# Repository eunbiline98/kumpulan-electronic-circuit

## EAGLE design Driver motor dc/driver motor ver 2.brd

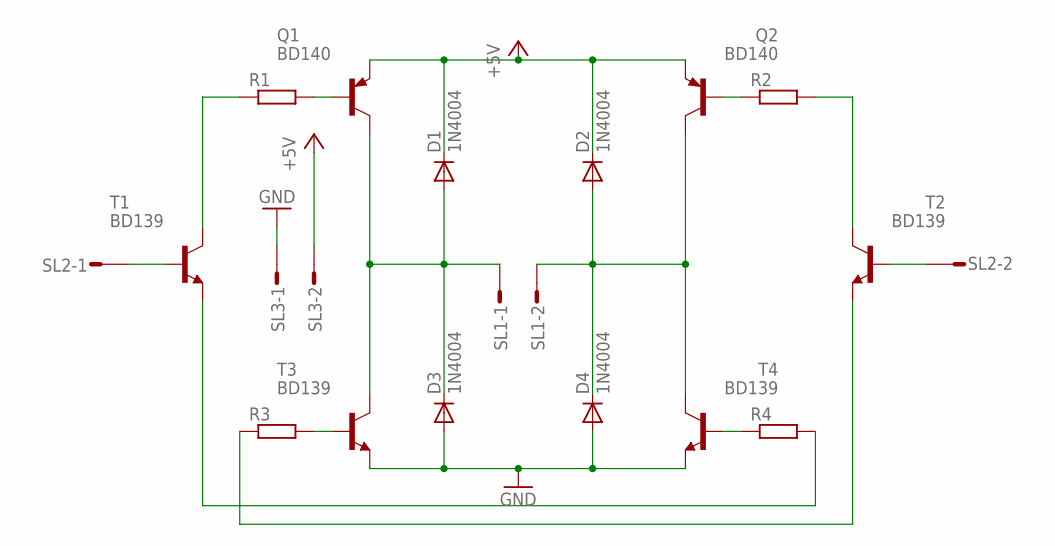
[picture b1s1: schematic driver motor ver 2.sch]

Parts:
D1, D2, D3, D4: 1N4004; DO41-10
Q1, Q2: BD140; TO126
R1, R2, R3, R4: R-EU_0204/5; 0204/5
SL1, SL2, SL3: M02S; 02P
T1, T2, T3, T4: BD139; TO126

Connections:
+5V: D1.C, D2.C, Q1.1 (E), Q2.1 (E), SL3.2
GND: D3.A, D4.A, SL3.1, T3.1 (E), T4.1 (E)
unnamed: Q1.3 (B), R1.2
unnamed: Q2.3 (B), R2.1
unnamed: R3.2, T3.3 (B)
unnamed: SL2.1, T1.3 (B)
unnamed: SL2.2, T2.3 (B)
unnamed: R1.1, T1.2 (C)
unnamed: D1.A, D3.C, Q1.2 (C), SL1.1, T3.2 (C)
unnamed: D2.A, D4.C, Q2.2 (C), SL1.2, T4.2 (C)
unnamed: R4.2, T1.1 (E)
unnamed: R4.1, T4.3 (B)
unnamed: R3.1, T2.1 (E)
unnamed: R2.2, T2.2 (C)

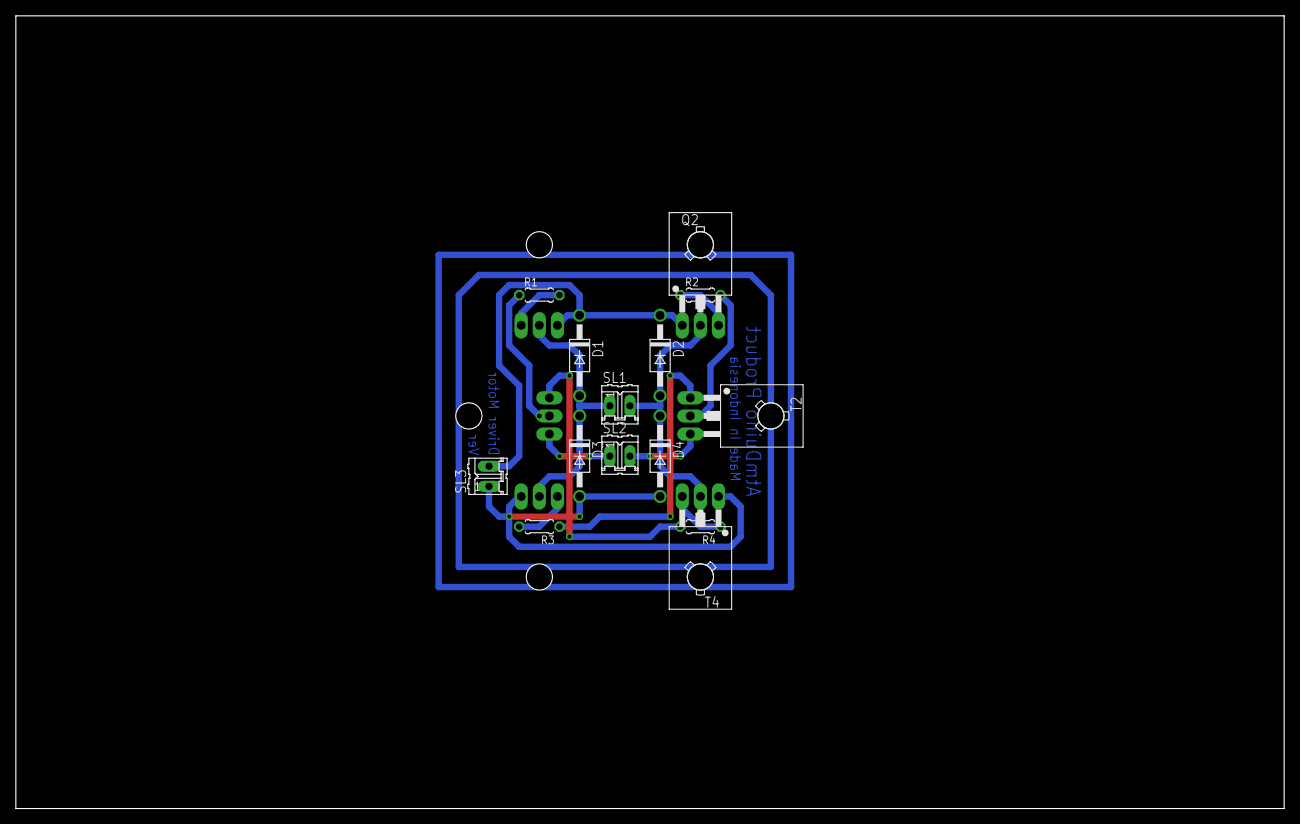
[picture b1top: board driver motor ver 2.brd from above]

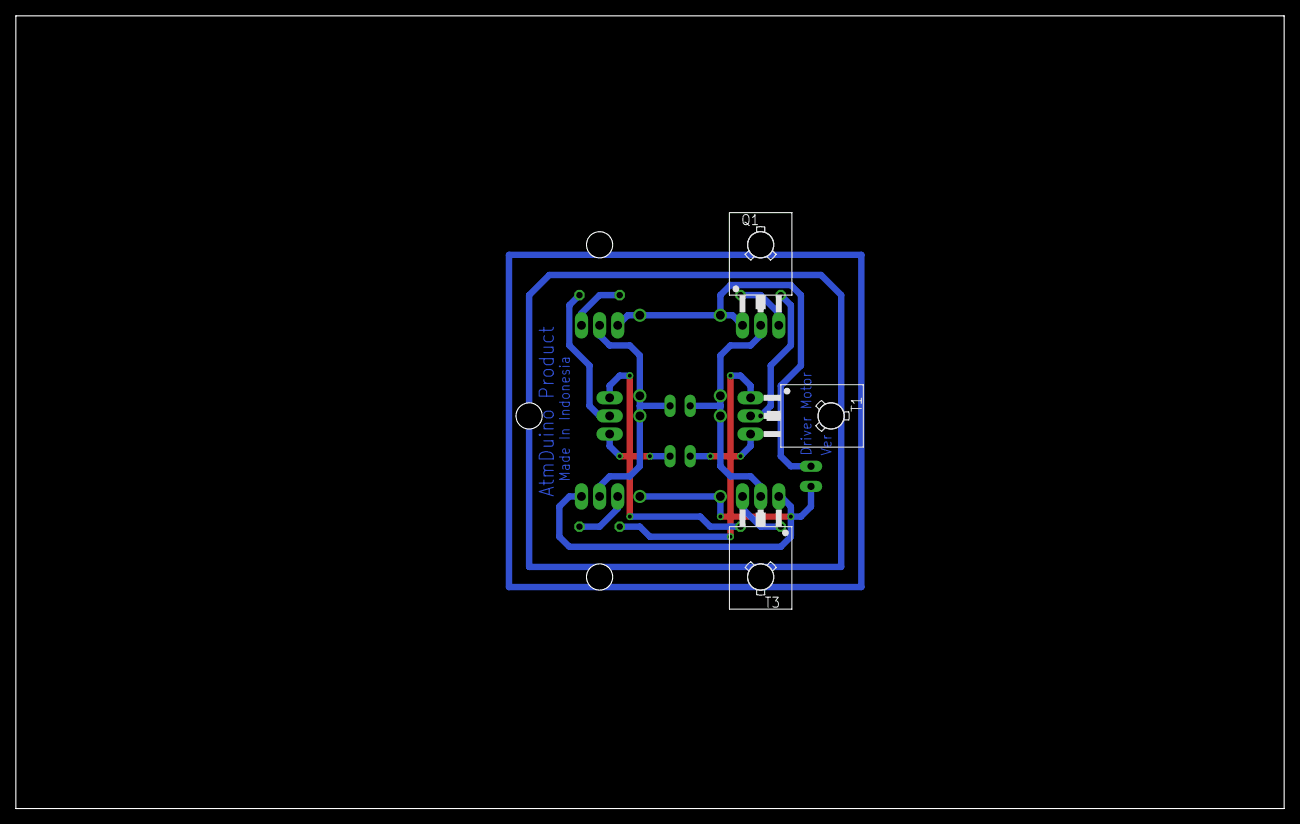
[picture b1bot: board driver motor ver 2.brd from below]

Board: 2 copper layers, 160.0 x 100.0 mm, 17 parts (3 on the bottom side), 14 nets.

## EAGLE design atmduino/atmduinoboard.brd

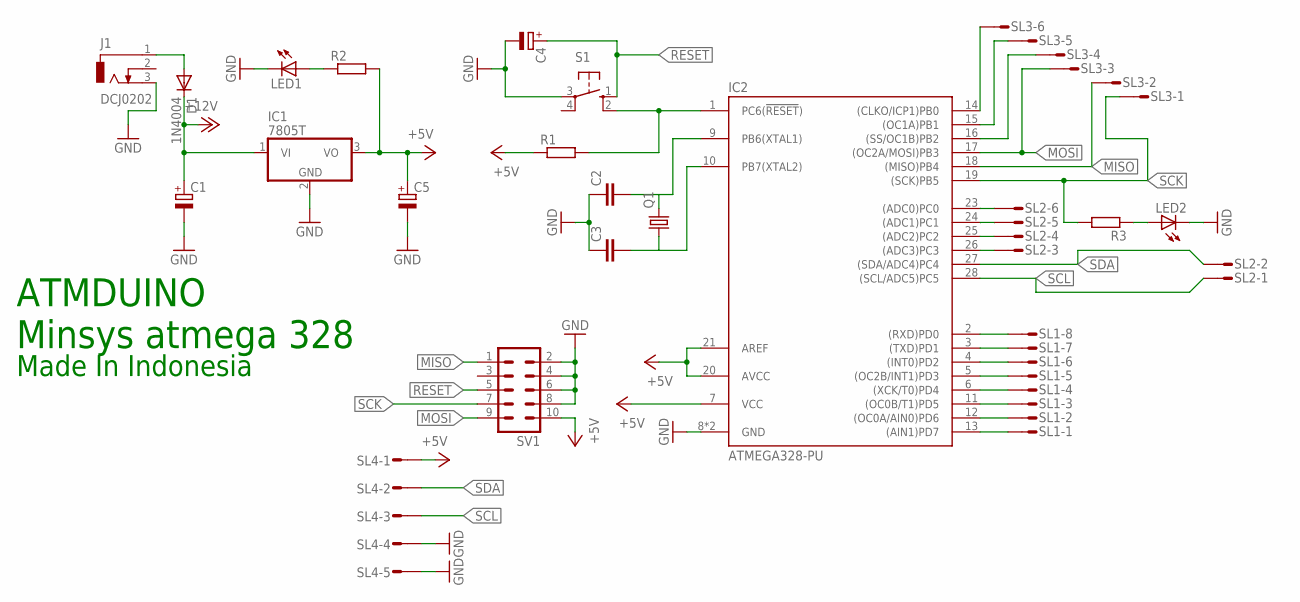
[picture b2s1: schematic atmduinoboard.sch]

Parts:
C1, C4, C5: CPOL-EUE2-4; E2-4
C2, C3: C-EU025-024X044; C025-024X044
D1: 1N4004; DO41-10
IC1: 7805T; TO220H
IC2: ATMEGA328-PU; DIL28
J1: DCJ0202
LED1, LED2: LED3MM
Q1: CRYSTALHC49U-V; HC49U-V
R1, R2, R3: R-EU_0204/5; 0204/5
S1: 10-XX; B3F-10XX
SL1: M08S; 08P
SL2, SL3, SL4: M06S; 06P
SV1: ML10

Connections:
+5V: C5.+, IC1.3 (VO), IC2.7 (VCC), IC2.20 (AVCC), IC2.21 (AREF), R1.1, R2.2, SL4.1, SV1.10
+12V: C1.+, D1.C, IC1.1 (VI)
GND: C1.-, C2.1, C3.1, C4.-, C5.-, IC1.2 (GND), IC2.8 (GND), IC2.22 (GND), J1.3, LED1.K (C), LED2.K (C), S1.3, SL4.4, SL4.5, SV1.2, SV1.4, SV1.6, SV1.8
MISO: IC2.18 ((MISO)PB4), SL3.2, SV1.1
MOSI: IC2.17 ((OC2A/MOSI)PB3), SL3.3, SV1.9
unnamed: LED1.A, R2.1
unnamed: LED2.A, R3.1
unnamed: IC2.2 ((RXD)PD0), SL1.8
unnamed: IC2.1 (PC6(!RESET!)), R1.2, S1.2 (S1)
unnamed: IC2.3 ((TXD)PD1), SL1.7
unnamed: C2.2, IC2.9 (PB6(XTAL1)), Q1.2
unnamed: C3.2, IC2.10 (PB7(XTAL2)), Q1.1
unnamed: IC2.4 ((INT0)PD2), SL1.6
unnamed: IC2.5 ((OC2B/INT1)PD3), SL1.5
unnamed: IC2.6 ((XCK/T0)PD4), SL1.4
unnamed: IC2.11 ((OC0B/T1)PD5), SL1.3
unnamed: IC2.12 ((OC0A/AIN0)PD6), SL1.2
unnamed: IC2.13 ((AIN1)PD7), SL1.1
unnamed: IC2.23 ((ADC0)PC0), SL2.6
unnamed: IC2.24 ((ADC1)PC1), SL2.5
unnamed: IC2.26 ((ADC3)PC3), SL2.3
unnamed: IC2.25 ((ADC2)PC2), SL2.4
unnamed: D1.A, J1.1
unnamed: IC2.14 ((CLKO/ICP1)PB0), SL3.6
unnamed: IC2.15 ((OC1A)PB1), SL3.5
unnamed: IC2.16 ((SS/OC1B)PB2), SL3.4
RESET: C4.+, S1.1 (S), SV1.5
SCK: IC2.19 ((SCK)PB5), R3.2, SL3.1, SV1.7
SCL: IC2.28 ((SCL/ADC5)PC5), SL2.1, SL4.3
SDA: IC2.27 ((SDA/ADC4)PC4), SL2.2, SL4.2

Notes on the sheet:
ATMDUINO
Minsys atmega 328
Made In Indonesia

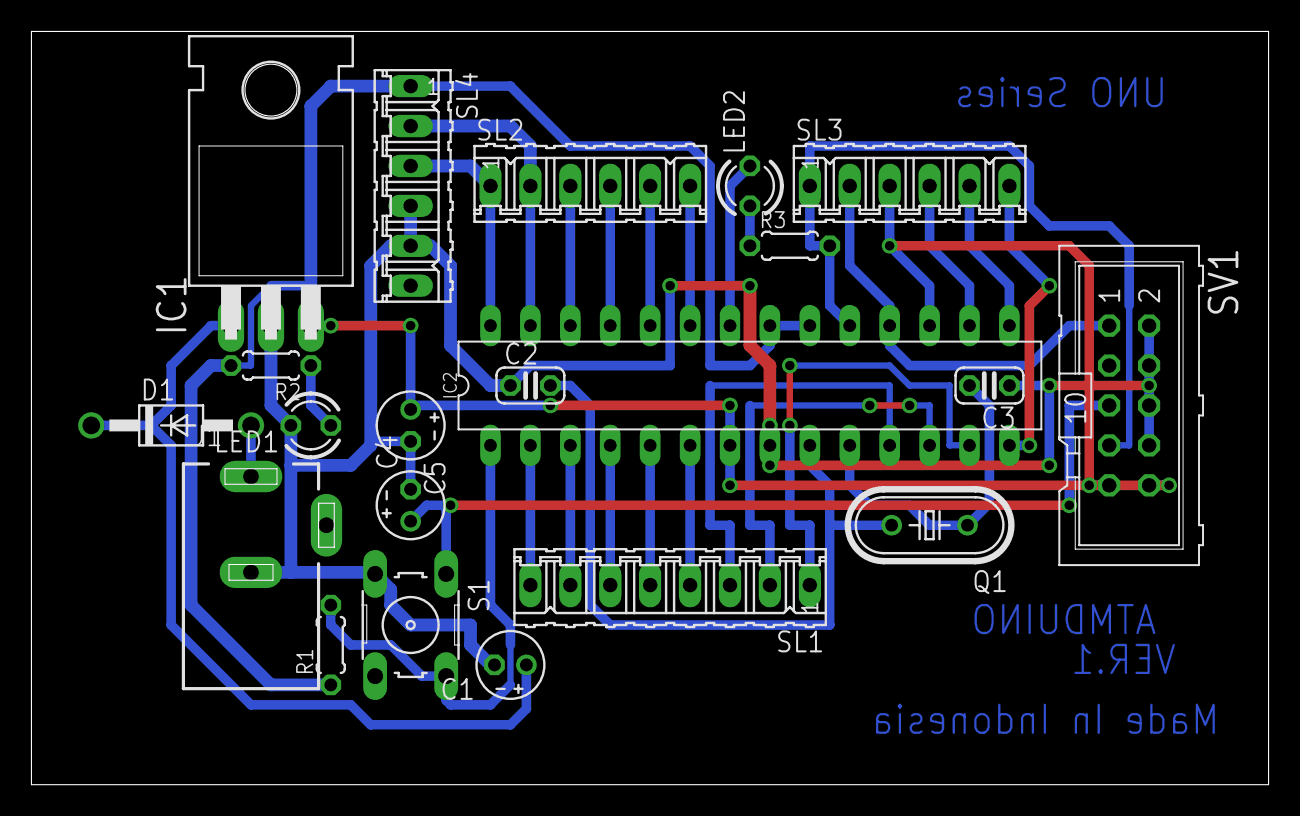
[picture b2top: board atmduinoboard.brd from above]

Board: 2 copper layers, 78.7 x 47.9 mm, 21 parts (0 on the bottom side), 30 nets.

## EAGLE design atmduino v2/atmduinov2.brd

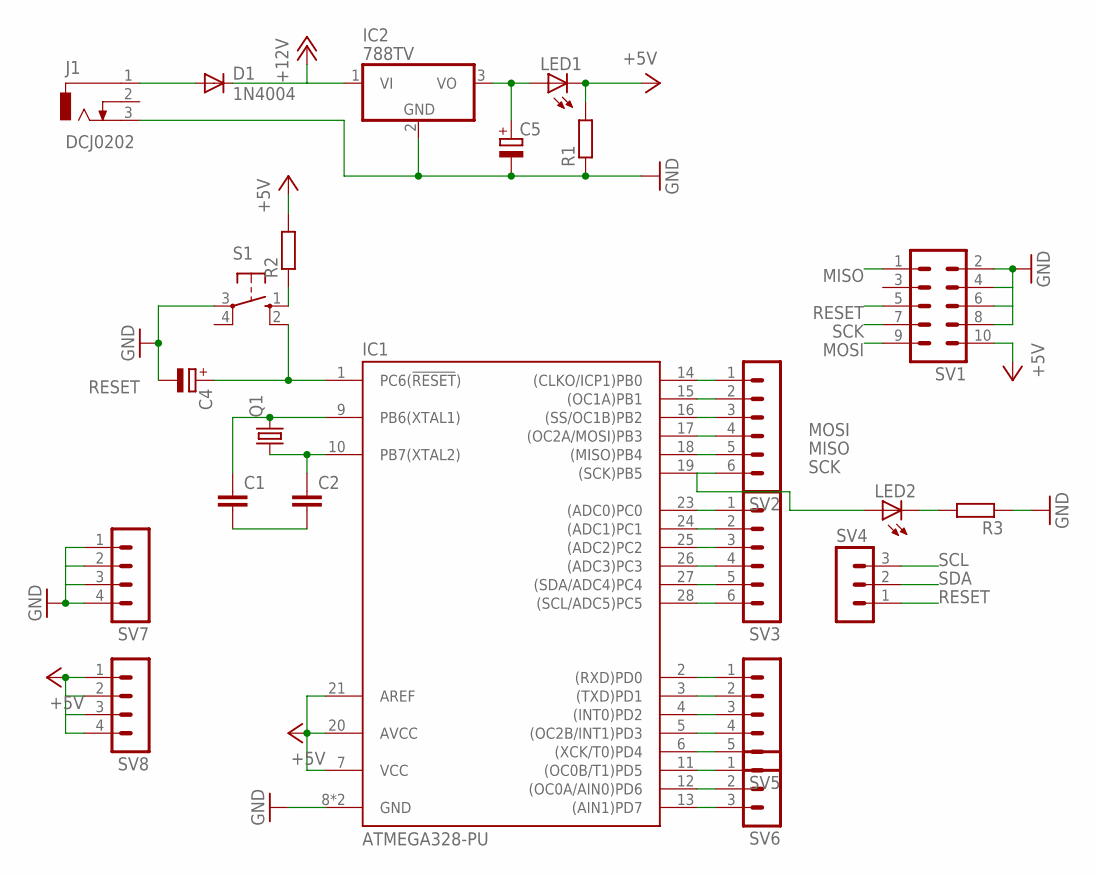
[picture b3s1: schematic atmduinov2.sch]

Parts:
C1, C2: C-EU025-024X044; C025-024X044
C4, C5: CPOL-EUE1.8-4; E1,8-4
D1: 1N4004; DO41-10
IC1: ATMEGA328-PU; DIL28
IC2: 788TV; TO220V
J1: DCJ0202
LED1, LED2: LED3MM
Q1: CRYSTALHC49S; HC49/S
R1, R2, R3: R-EU_0204/5; 0204/5
S1: 10-XX; B3F-10XX
SV1: ML10
SV2, SV3: MA06-1
SV4, SV6: MA03-1
SV5: MA05-1
SV7, SV8: MA04-1

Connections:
+5V: IC1.7 (VCC), IC1.20 (AVCC), IC1.21 (AREF), LED1.K (C), R1.2, R2.2, SV1.10, SV8.1, SV8.2, SV8.3, SV8.4
+12V: D1.C, IC2.1 (VI)
GND: C4.-, C5.-, IC1.8 (GND), IC1.22 (GND), IC2.2 (GND), J1.3, R1.1, R3.1, S1.3, SV1.2, SV1.4, SV1.6, SV1.8, SV7.1, SV7.2, SV7.3, SV7.4
MISO: IC1.18 ((MISO)PB4), SV1.1, SV2.5
MOSI: IC1.17 ((OC2A/MOSI)PB3), SV1.9, SV2.4
unnamed: D1.A, J1.1
unnamed: C5.+, IC2.3 (VO), LED1.A
unnamed: LED2.K (C), R3.2
unnamed: IC1.14 ((CLKO/ICP1)PB0), SV2.1
unnamed: IC1.15 ((OC1A)PB1), SV2.2
unnamed: IC1.16 ((SS/OC1B)PB2), SV2.3
unnamed: IC1.23 ((ADC0)PC0), SV3.1
unnamed: IC1.24 ((ADC1)PC1), SV3.2
unnamed: IC1.25 ((ADC2)PC2), SV3.3
unnamed: IC1.26 ((ADC3)PC3), SV3.4
unnamed: IC1.2 ((RXD)PD0), SV5.1
unnamed: IC1.3 ((TXD)PD1), SV5.2
unnamed: IC1.4 ((INT0)PD2), SV5.3
unnamed: IC1.5 ((OC2B/INT1)PD3), SV5.4
unnamed: IC1.6 ((XCK/T0)PD4), SV5.5
unnamed: IC1.11 ((OC0B/T1)PD5), SV6.1
unnamed: IC1.12 ((OC0A/AIN0)PD6), SV6.2
unnamed: IC1.13 ((AIN1)PD7), SV6.3
unnamed: C2.1, IC1.10 (PB7(XTAL2)), Q1.1
unnamed: C1.1, IC1.9 (PB6(XTAL1)), Q1.2
unnamed: C1.2, C2.2
unnamed: R2.1, S1.1 (S)
RESET: C4.+, IC1.1 (PC6(!RESET!)), S1.2 (S1), SV1.5, SV4.1
SCK: IC1.19 ((SCK)PB5), LED2.A, SV1.7, SV2.6
SCL: IC1.28 ((SCL/ADC5)PC5), SV3.6, SV4.3
SDA: IC1.27 ((SDA/ADC4)PC4), SV3.5, SV4.2

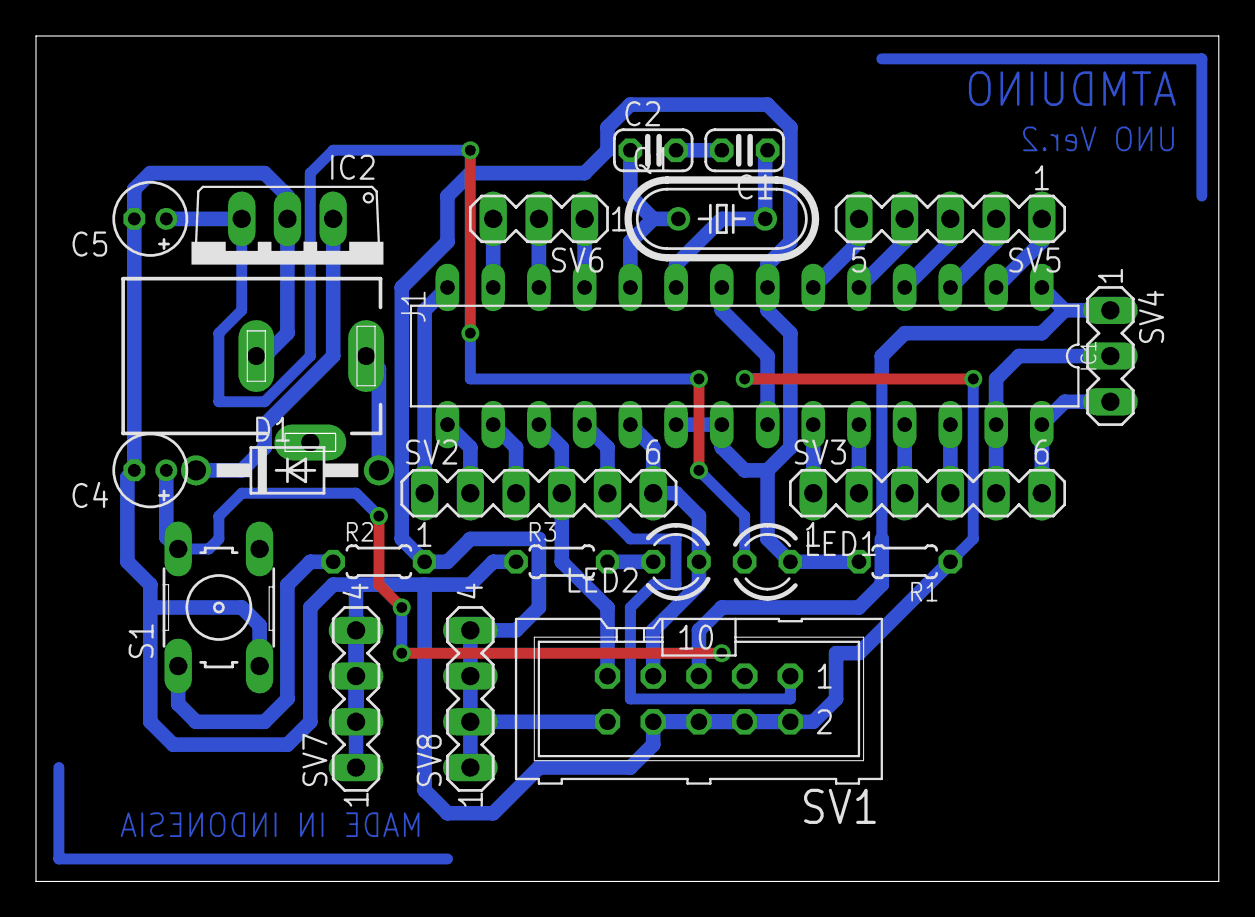
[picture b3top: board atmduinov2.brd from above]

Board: 2 copper layers, 65.7 x 47.0 mm, 23 parts (0 on the bottom side), 31 nets.

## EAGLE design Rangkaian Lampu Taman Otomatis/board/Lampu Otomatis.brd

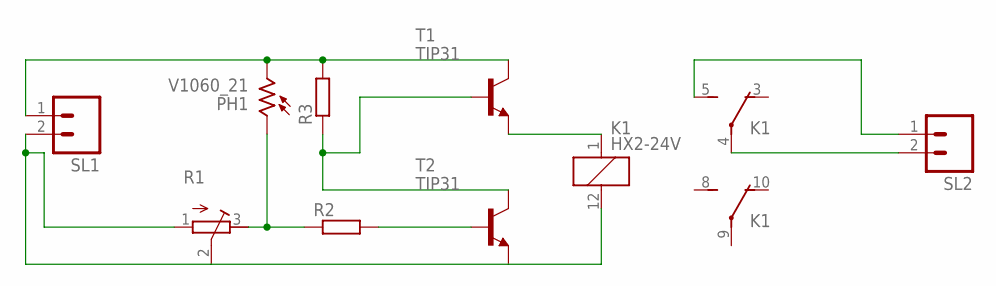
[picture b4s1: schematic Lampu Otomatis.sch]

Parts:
K1: HX2-24V; HX
PH1: V1060_21; TO-5_V10
R1: R-TRIMM3339P; RTRIM3339P
R2, R3: R-EU_0207/10; 0207/10
SL1, SL2: M02; 02P
T1, T2: TIP31; TO220

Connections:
unnamed: PH1.2, R3.2, SL1.1, T1.2 (C)
unnamed: K1.1, T1.3 (E)
unnamed: R2.2, T2.1 (B)
unnamed: PH1.1, R1.3 (E), R2.1
unnamed: R3.1, T1.1 (B), T2.2 (C)
unnamed: K1.12 (2), R1.1 (A), R1.2 (S), SL1.2, T2.3 (E)
unnamed: K1.5 (S), SL2.1
unnamed: K1.4, SL2.2

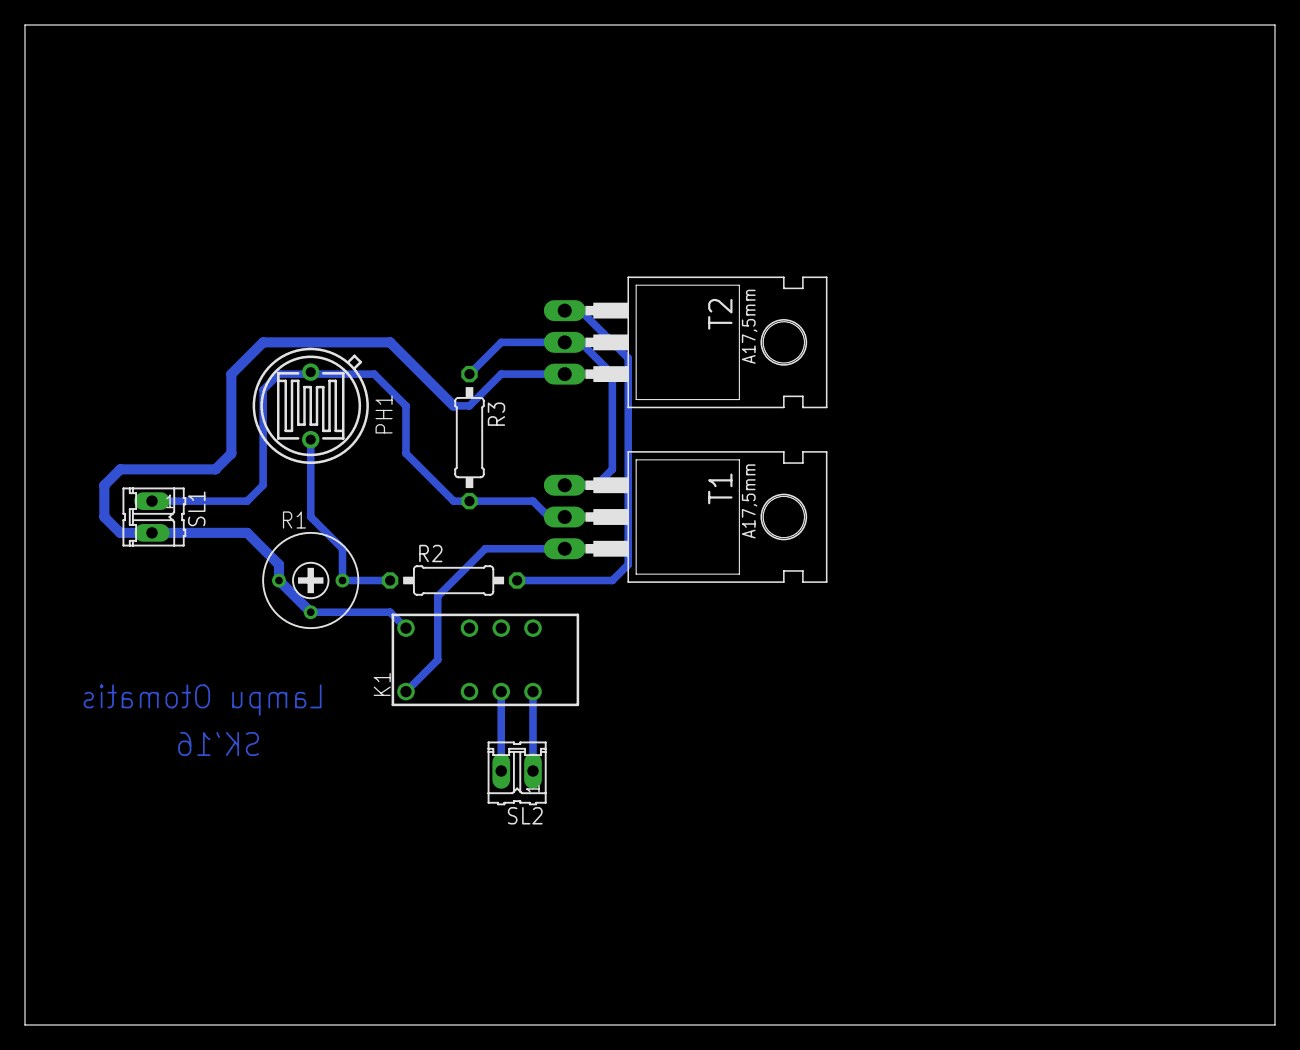
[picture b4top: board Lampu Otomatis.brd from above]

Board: 2 copper layers, 100.0 x 80.0 mm, 9 parts (0 on the bottom side), 8 nets.

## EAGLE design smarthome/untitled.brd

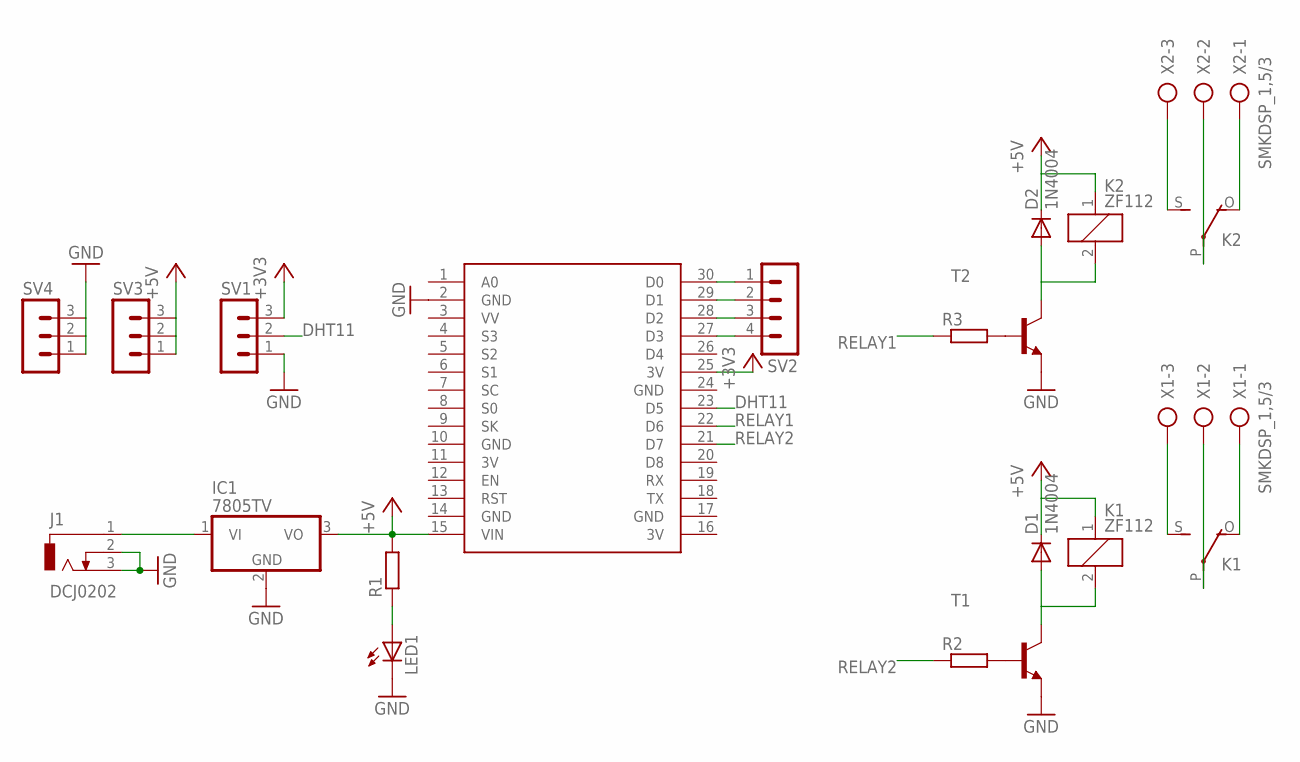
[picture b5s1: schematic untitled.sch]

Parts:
D1, D2: 1N4004; DO41-10
IC1: 7805TV; TO220V
J1: DCJ0202
K1, K2: ZF112
LED1: LED5MM
R1, R2, R3: R-EU_0207/10; 0207/10
SV1, SV3, SV4: MA03-1
SV2: MA04-1
T1, T2: 2N2222-NPN-TO18-EBC; TO18
U$1: NODEMCU
X1, X2: SMKDSP_1,5/3

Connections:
3V: U$1.11 (3V), U$1.16 (3V)
+3V3: SV1.3, U$1.25 (3V)
+5V: D1.C, D2.C, IC1.3 (VO), K1.1, K2.1, R1.2, SV3.1, SV3.2, SV3.3, U$1.15 (VIN)
DHT11: SV1.2, U$1.23 (D5)
GND: IC1.2 (GND), J1.2, J1.3, LED1.K (C), SV1.1, SV4.1, SV4.2, SV4.3, T1.1 (E), T2.1 (E), U$1.2 (GND), U$1.10 (GND), U$1.14 (GND), U$1.17 (GND), U$1.24 (GND)
unnamed: K1.S, X1.3
unnamed: LED1.A, R1.1
unnamed: IC1.1 (VI), J1.1
unnamed: D1.A, K1.2, T1.3 (C)
unnamed: K1.O, X1.1
unnamed: SV2.1, U$1.30 (D0)
unnamed: SV2.2, U$1.29 (D1)
unnamed: SV2.3, U$1.28 (D2)
unnamed: SV2.4, U$1.27 (D3)
unnamed: K1.P, X1.2
unnamed: R2.2, T1.2 (B)
unnamed: D2.A, K2.2, T2.3 (C)
unnamed: R3.2, T2.2 (B)
unnamed: K2.S, X2.3
unnamed: K2.O, X2.1
unnamed: K2.P, X2.2
RELAY1: R3.1, U$1.22 (D6)
RELAY2: R2.1, U$1.21 (D7)

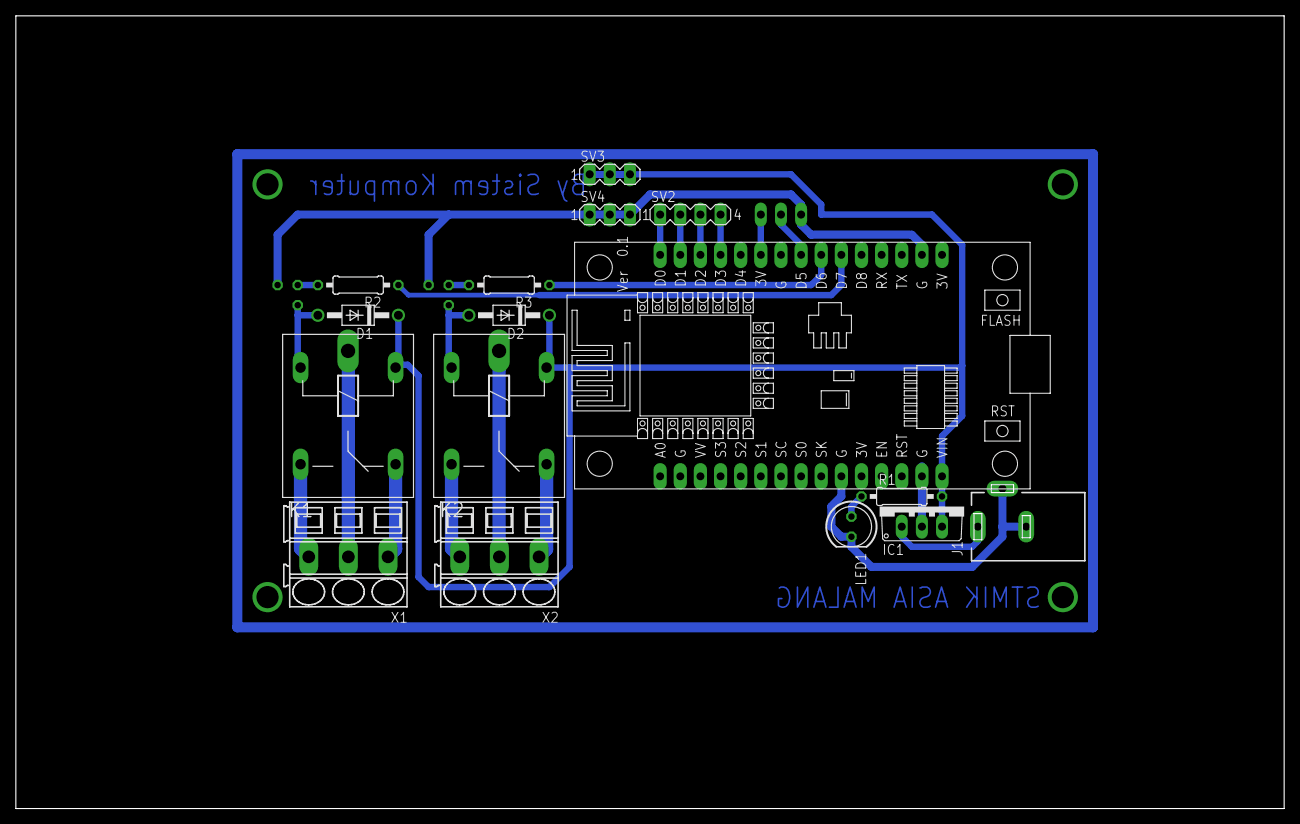
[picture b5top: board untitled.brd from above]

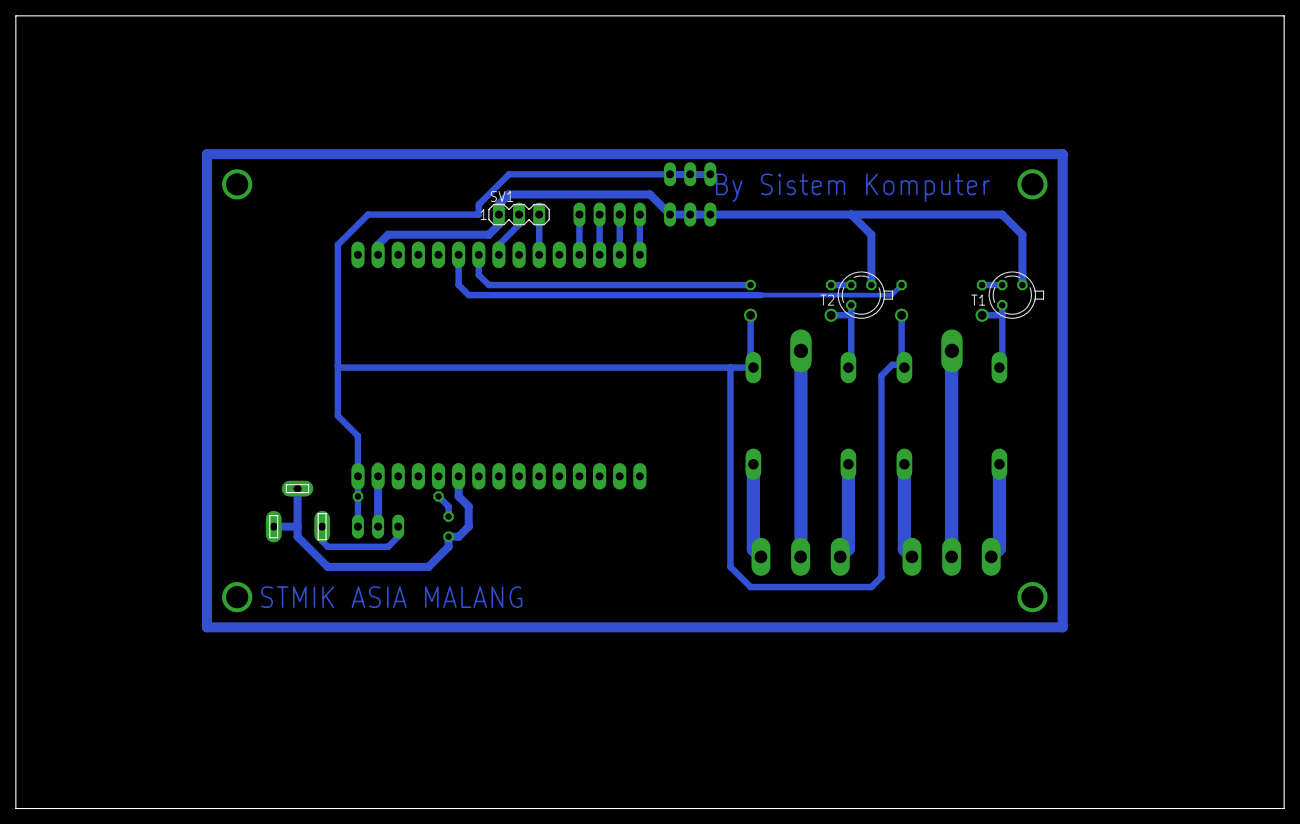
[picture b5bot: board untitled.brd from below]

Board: 2 copper layers, 160.0 x 100.0 mm, 19 parts (3 on the bottom side), 23 nets.

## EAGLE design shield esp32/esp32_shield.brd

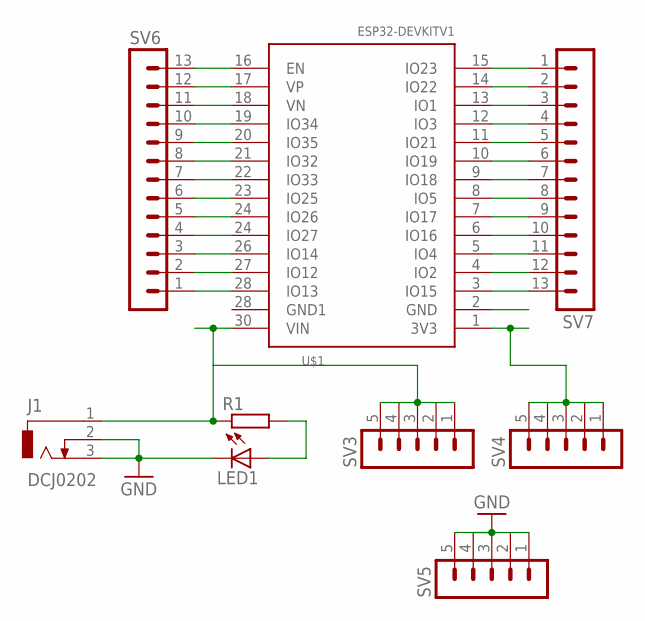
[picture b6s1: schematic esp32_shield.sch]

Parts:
J1: DCJ0202
LED1: LED5MM
R1: R-EU_0204/7; 0204/7
SV3, SV4, SV5: MA05-1
SV6, SV7: MA13-1
U$1: ESP32DEVKITV1; ESP32-DEVKITV1

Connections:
GND: J1.2, J1.3, LED1.K (C), SV5.1, SV5.2, SV5.3, SV5.4, SV5.5
unnamed: SV7.1, U$1.15 (IO23)
unnamed: SV7.2, U$1.14 (IO22)
unnamed: SV7.3, U$1.13 (IO1)
unnamed: SV7.4, U$1.12 (IO3)
unnamed: SV7.5, U$1.11 (IO21)
unnamed: SV7.6, U$1.10 (IO19)
unnamed: SV7.7, U$1.9 (IO18)
unnamed: SV7.8, U$1.8 (IO5)
unnamed: SV7.9, U$1.7 (IO17)
unnamed: SV7.10, U$1.6 (IO16)
unnamed: SV7.11, U$1.5 (IO4)
unnamed: SV7.12, U$1.4 (IO2)
unnamed: SV7.13, U$1.3 (IO15)
unnamed: SV4.1, SV4.2, SV4.3, SV4.4, SV4.5, U$1.1 (3V3)
unnamed: J1.1, R1.1, SV3.1, SV3.2, SV3.3, SV3.4, SV3.5, U$1.30 (VIN)
unnamed: SV6.2, U$1.27 (IO12)
unnamed: SV6.3, U$1.26 (IO14)
unnamed: SV6.6, U$1.23 (IO25)
unnamed: SV6.7, U$1.22 (IO33)
unnamed: SV6.8, U$1.21 (IO32)
unnamed: SV6.9, U$1.20 (IO35)
unnamed: SV6.10, U$1.19 (IO34)
unnamed: SV6.11, U$1.18 (VN)
unnamed: SV6.12, U$1.17 (VP)
unnamed: SV6.13, U$1.16 (EN)
unnamed: SV6.1, U$1.28 (IO13)
unnamed: LED1.A, R1.2

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
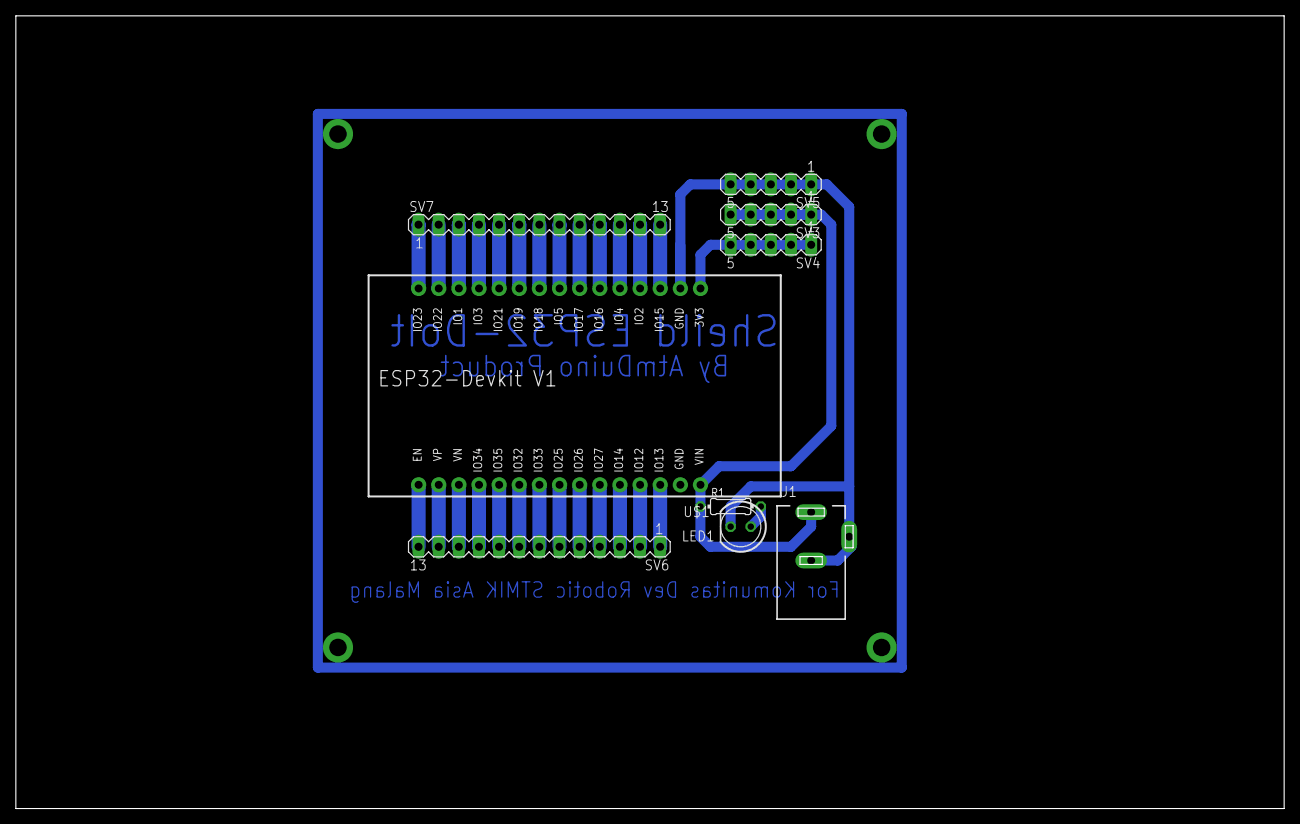
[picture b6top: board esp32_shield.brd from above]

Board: 2 copper layers, 160.0 x 100.0 mm, 9 parts (0 on the bottom side), 30 nets.

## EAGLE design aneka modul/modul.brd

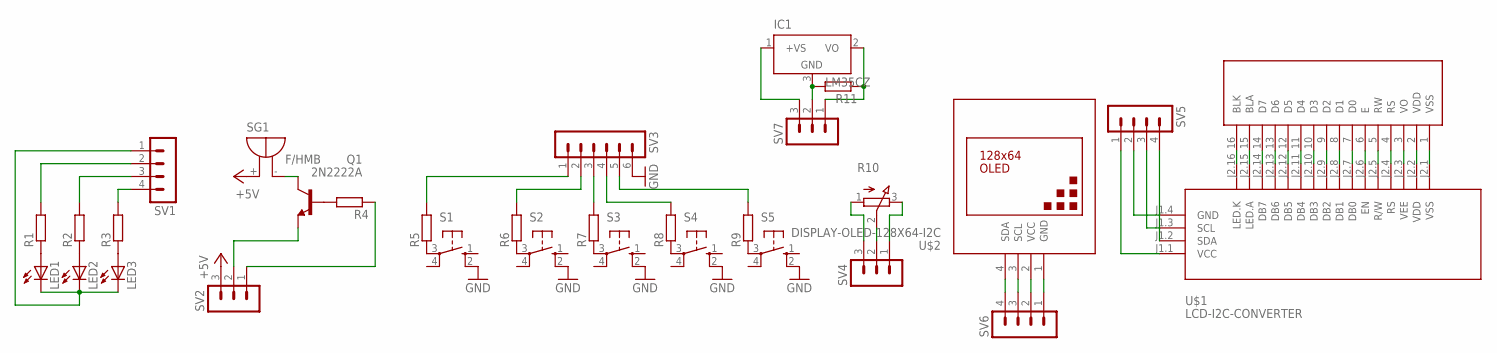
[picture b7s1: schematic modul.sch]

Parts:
IC1: LM35CZ; TO92
LED1, LED2, LED3: LED10MM
Q1: 2N2222A; TO18
R1, R2, R3, R4, R5, R6, R7, R8, R9, R11: R-EU_0204/5; 0204/5
R10: 3RP/1610N
S1, S2, S3, S4, S5: 10-XX; B3F-10XX
SG1: F/HMB
SV1, SV5, SV6: MA04-1
SV2, SV4, SV7: MA03-1
SV3: MA06-1
U$1: LCD-I2C-CONVERTER
U$2: DISPLAY-OLED-128X64-I2C
U$3: 2X16LCDTOP

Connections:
+5V: SG1.+, SV2.3
GND: S1.2 (S1), S2.2 (S1), S3.2 (S1), S4.2 (S1), S5.2 (S1), SV3.6
unnamed: LED1.A, R1.1
unnamed: LED2.A, R2.1
unnamed: LED3.A, R3.1
unnamed: R3.2, SV1.4
unnamed: R2.2, SV1.3
unnamed: R1.2, SV1.2
unnamed: Q1.3 (C), SG1.-
unnamed: Q1.2 (B), R4.2
unnamed: R4.1, SV2.1
unnamed: Q1.1 (E), SV2.2
unnamed: LED1.K (C), LED2.K (C), LED3.K (C), SV1.1
unnamed: R5.1, S1.3
unnamed: R6.1, S2.3
unnamed: R7.1, S3.3
unnamed: R8.1, S4.3
unnamed: R9.1, S5.3
unnamed: R5.2, SV3.1
unnamed: R6.2, SV3.2
unnamed: R7.2, SV3.3
unnamed: R8.2, SV3.4
unnamed: R9.2, SV3.5
unnamed: R10.2 (S), SV4.2
unnamed: R10.3 (E), SV4.1
unnamed: R10.1 (A), SV4.3
unnamed: U$1.J2.1 (VSS), U$3.1 (VSS)
unnamed: U$1.J2.2 (VDD), U$3.2 (VDD)
unnamed: U$1.J2.3 (VEE), U$3.3 (VO)
unnamed: U$1.J2.4 (RS), U$3.4 (RS)
unnamed: U$1.J2.5 (R/W), U$3.5 (RW)
unnamed: U$1.J2.6 (EN), U$3.6 (E)
unnamed: U$1.J2.7 (DB0), U$3.7 (D0)
unnamed: U$1.J2.8 (DB1), U$3.8 (D1)
unnamed: U$1.J2.9 (DB2), U$3.9 (D2)
unnamed: U$1.J2.10 (DB3), U$3.10 (D3)
unnamed: U$1.J2.11 (DB4), U$3.11 (D4)
unnamed: U$1.J2.12 (DB5), U$3.12 (D5)
unnamed: U$1.J2.13 (DB6), U$3.13 (D6)
unnamed: U$1.J2.14 (DB7), U$3.14 (D7)
unnamed: U$1.J2.15 (LED.A), U$3.15 (BLA)
unnamed: U$1.J2.16 (LED.K), U$3.16 (BLK)
unnamed: SV5.1, U$1.J1.1 (VCC)
unnamed: SV5.2, U$1.J1.4 (GND)
unnamed: SV5.3, U$1.J1.3 (SCL)
unnamed: SV5.4, U$1.J1.2 (SDA)
unnamed: SV6.1, U$2.1 (GND)
unnamed: SV6.2, U$2.2 (VCC)
unnamed: SV6.3, U$2.3 (SCL)
unnamed: SV6.4, U$2.4 (SDA)
unnamed: IC1.3 (GND), R11.2, SV7.2
unnamed: IC1.1 (+VS), SV7.3
unnamed: IC1.2 (VO), R11.1, SV7.1

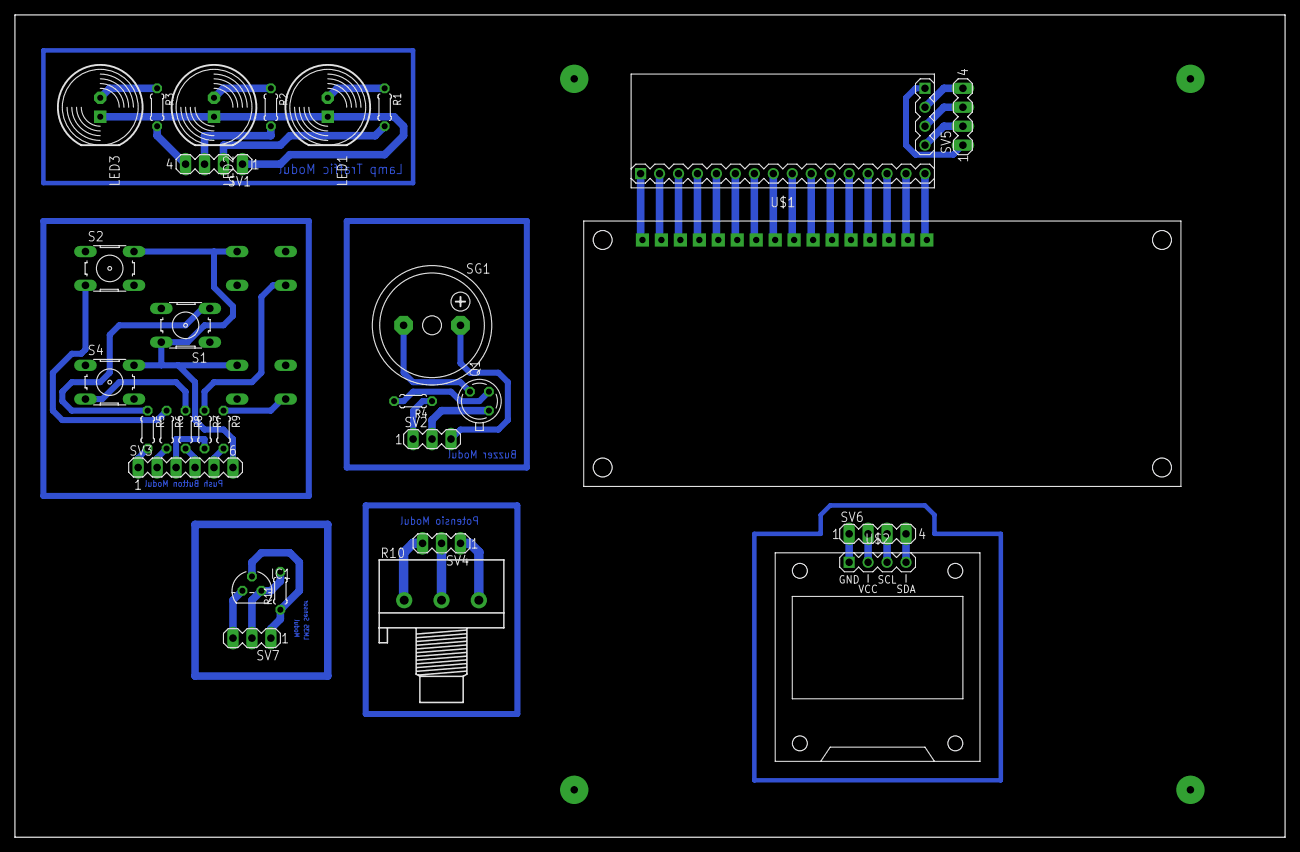
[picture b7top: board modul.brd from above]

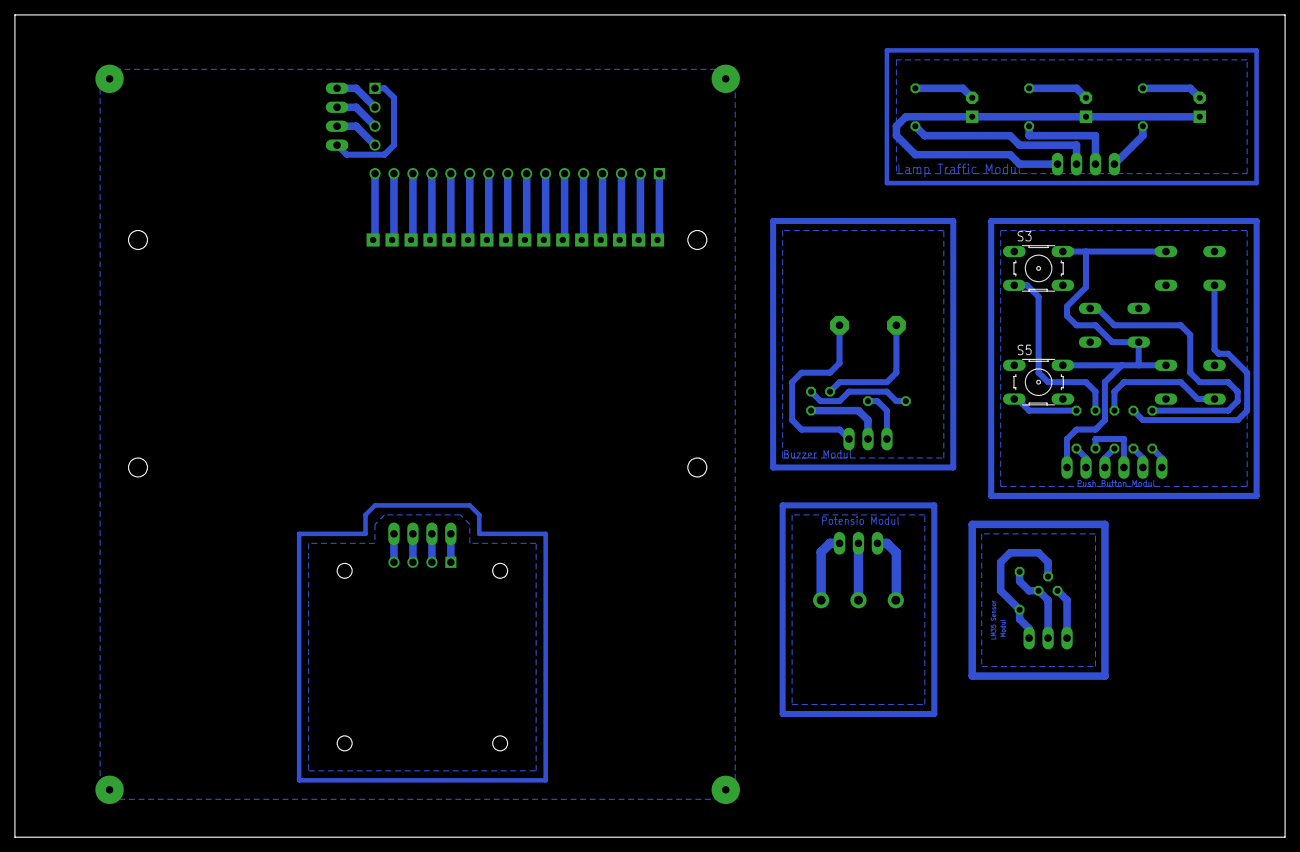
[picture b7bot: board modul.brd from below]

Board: 2 copper layers, 170.2 x 110.2 mm, 32 parts (2 on the bottom side), 53 nets.

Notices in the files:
parts and their libraries:
diy-modules: Released under the Creative Commons Attribution 4.0 International License: http://creativecommons.org/licenses/by/4.0
